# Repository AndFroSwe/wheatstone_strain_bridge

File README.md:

# wheatstone_strain_bridge
ECAD files for Wheatstone bridge to be used with strain gauges. Also has switchable calibration resistances.

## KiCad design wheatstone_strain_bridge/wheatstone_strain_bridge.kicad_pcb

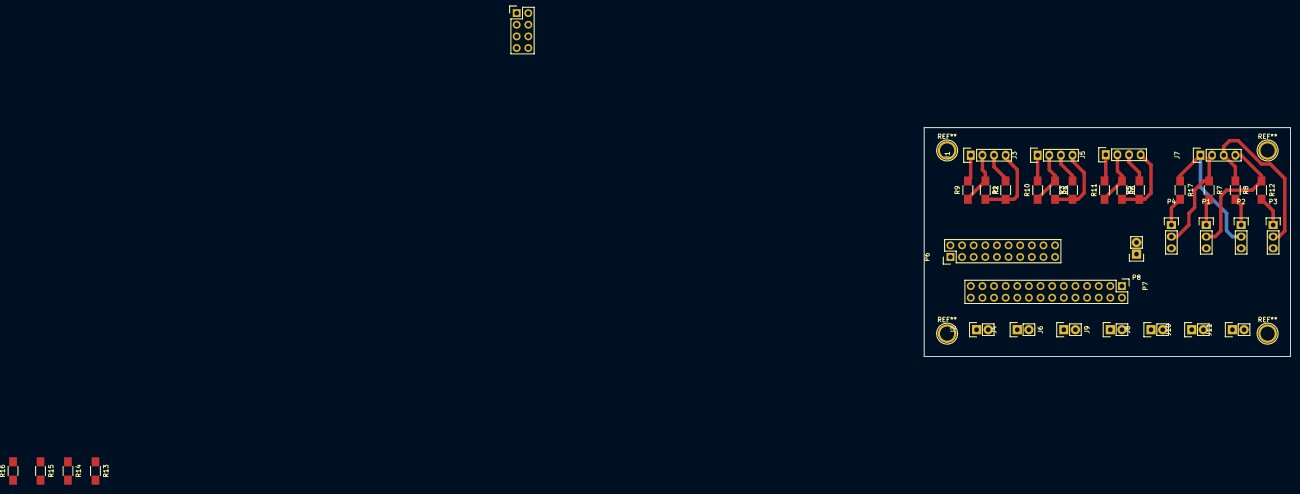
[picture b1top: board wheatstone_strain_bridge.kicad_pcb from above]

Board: 2 copper layers, 80.0 x 50.0 mm, 36 parts (0 on the bottom side), 36 nets.

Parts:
J1, J3, J5, J7: Conn_01x04; Pin_Header_Straight_1x04
J2, J4, J6, J8, J9, J10, J11: Conn_01x02; Pin_Header_Straight_1x02
P1, P2, P3, P4: CONN_01X03; Pin_Header_Straight_1x03
P5: CONN_02X04; Pin_Header_Straight_2x04
P6: CONN_02X10; Pin_Header_Straight_2x10
P7: CONN_02X14; Pin_Header_Straight_2x14
P8: CONN_01X02; Pin_Header_Straight_1x02
R1, R2, R3, R4, R5, R6, R7, R8, R9, R10, R11, R12, R17: 120; R_1206_HandSoldering
R13, R14, R15, R16: R; R_1206_HandSoldering

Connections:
/DC_1-GND: J1.2, R2.1, R9.1
/DC_1-VCC: J1.3, J2.1, P7.28, R1.2
/DC_2-GND: J3.2, R4.1, R10.1
/DC_2-VCC: J3.3, J4.1, P7.24, R3.2
/DC_3-GND: J5.2, R6.1, R11.1
/DC_3-VCC: J5.3, J6.1, P7.20, R5.2
/DC_4-GND: J7.2, J8.2, P4.2, P7.14, R7.1
/DC_4-VCC: J7.3, J10.2, P3.2, P7.6, R8.1
/GAUGE_1-2: J1.1, J2.2, P7.26, R9.2
/GAUGE_2-2: J3.1, J4.2, P7.22, R10.2
/GAUGE_3-2: J5.1, J6.2, P7.18, R11.2
/GAUGE_4-1: J8.1, P1.3, P7.16
/GAUGE_4-3: J9.1, P3.3, P7.12
/GAUGE_4-4: J7.4, J9.2, P1.2, P7.10, R12.1
/GAUGE_4-5: J10.1, P2.3, P7.8
/GAUGE_4-7: J11.1, P4.3, P7.4
/GAUGE_4-8: J7.1, J11.2, P2.2, P7.2, R17.1
/MEAS_1-2: J1.4, R1.1, R2.2
/MEAS_2-2: J3.4, R3.1, R4.2
/MEAS_3-2: J5.4, R5.1, R6.2
/R_CALIB_1-1: P6.2, R13.1
/R_CALIB_1-2: P6.4, R13.2
/R_CALIB_2-1: P6.6, R14.1
/R_CALIB_2-2: P6.8, R14.2
/R_CALIB_3-1: P6.10, R15.1
/R_CALIB_3-2: P6.12, R15.2
/R_CALIB_4-1: P6.14, R16.1
/R_CALIB_4-2: P6.16, R16.2
/R_CALIB_INPUT-1: P6.1, P6.5, P6.9, P6.13, P6.17, P7.1, P7.5, P7.9, P7.13, P7.17, P7.21, P7.25
/R_CALIB_INPUT-2: P6.3, P6.7, P6.11, P6.15, P6.19, P7.3, P7.7, P7.11, P7.15, P7.19, P7.23, P7.27
/R_CALIB_SOCKET-1: P6.18, P8.1
/R_CALIB_SOCKET-2: P6.20, P8.2
unnamed: P1.1, R7.2
unnamed: P2.1, R8.2
unnamed: P3.1, R12.2
unnamed: P4.1, R17.2

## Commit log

2018-01-03 First design version
2018-02-12 Working on new version with better jumper solution
